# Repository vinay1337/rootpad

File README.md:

# rootpad
A 18 key macropad / numpad based on the atmega32u4 microcontroller

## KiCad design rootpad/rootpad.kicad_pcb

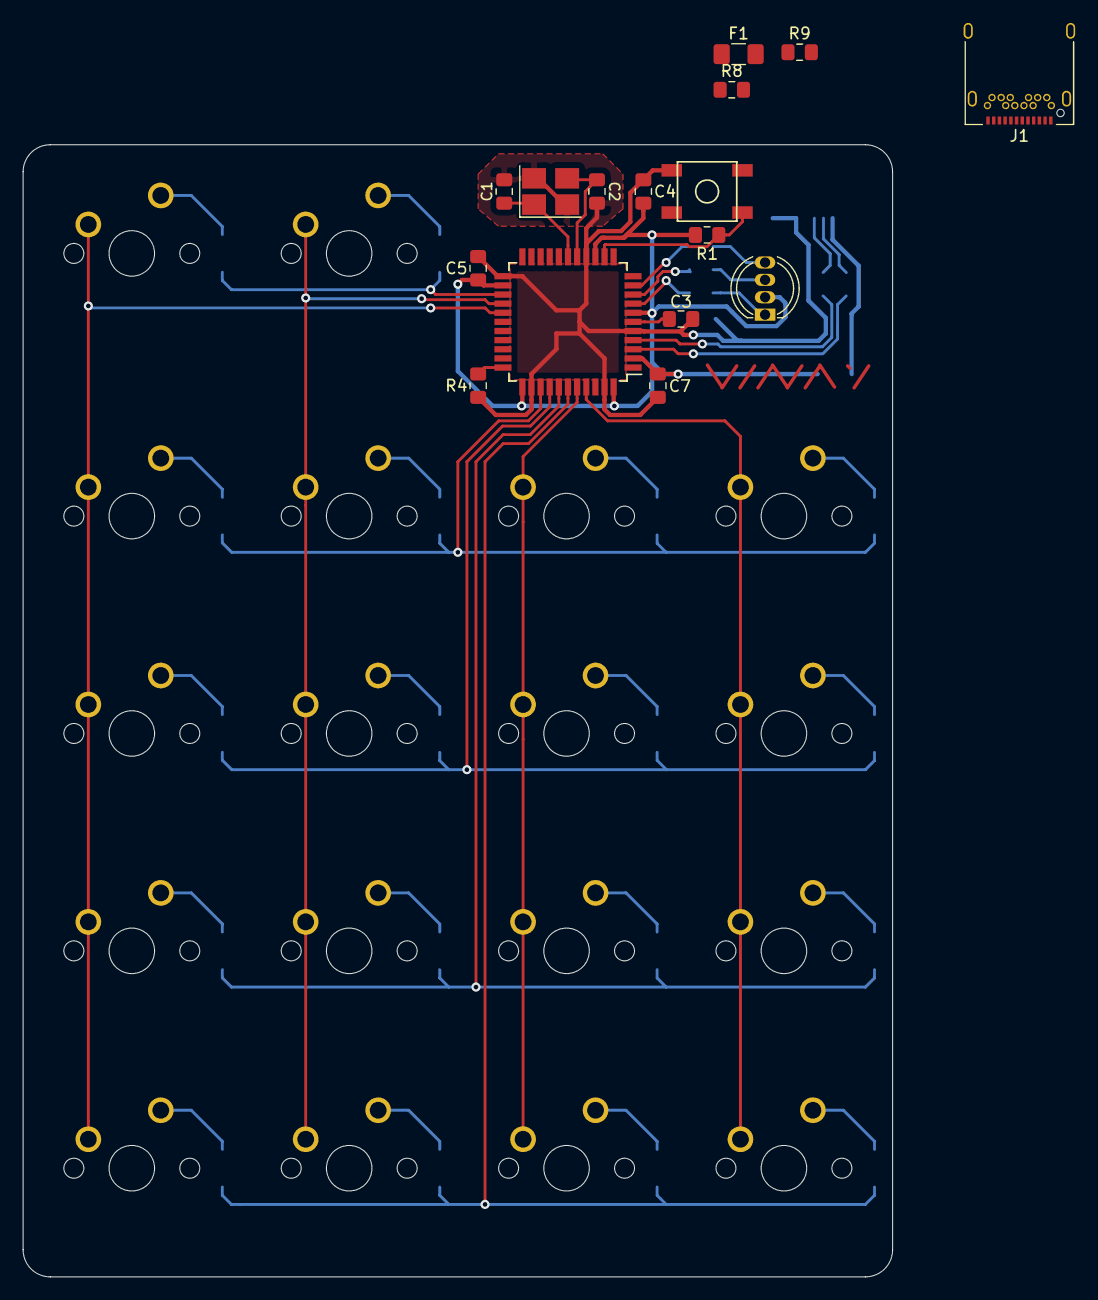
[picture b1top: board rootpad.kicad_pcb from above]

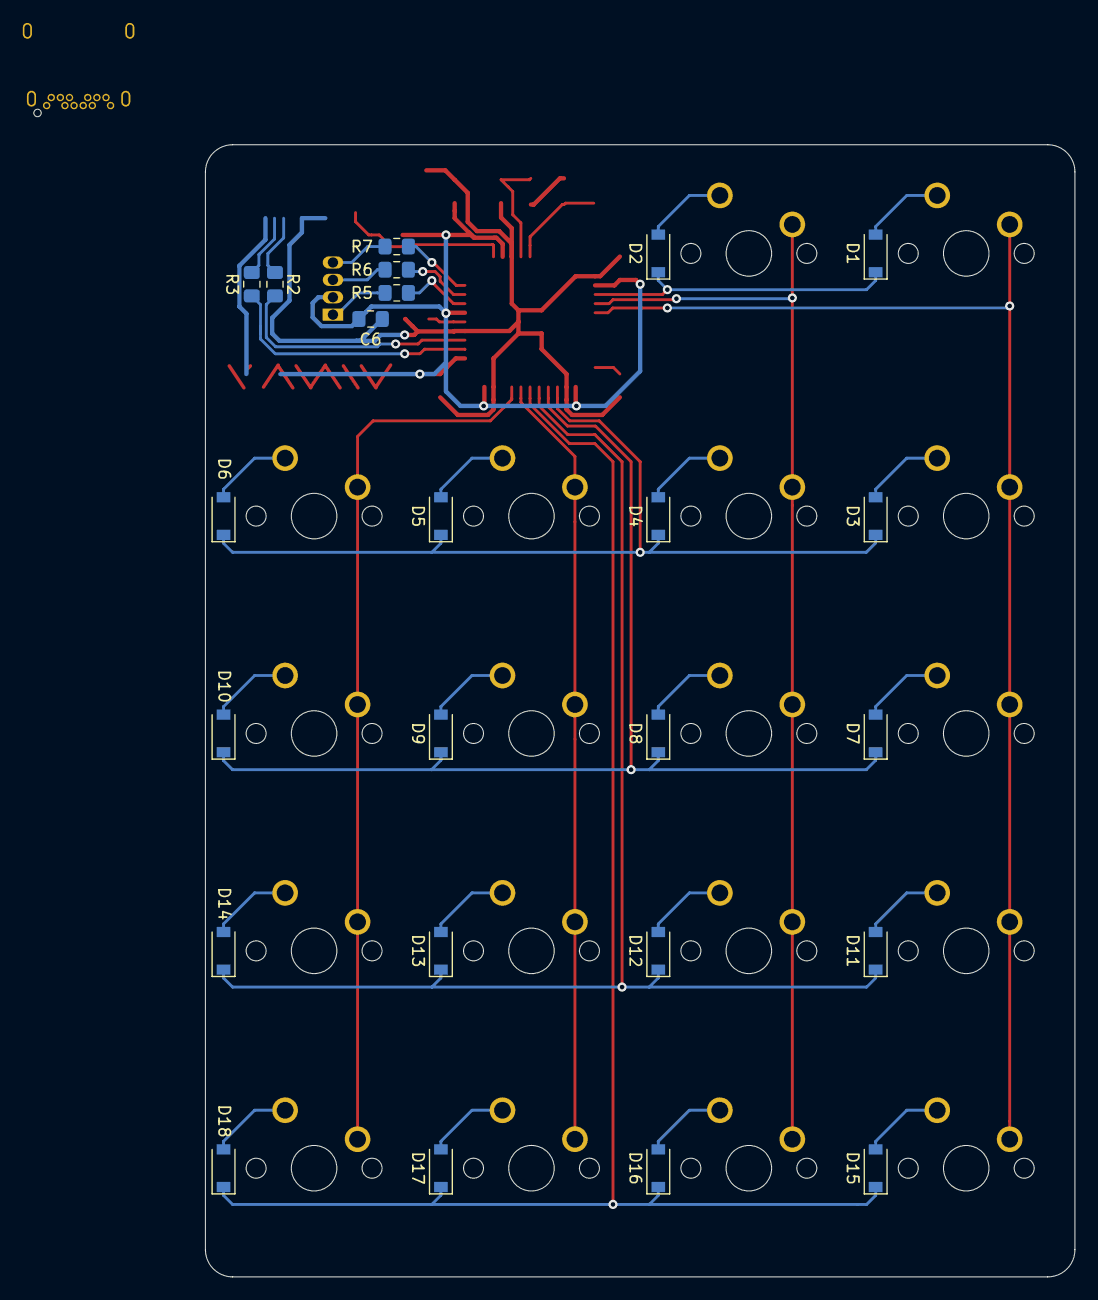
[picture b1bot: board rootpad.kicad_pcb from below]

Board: 2 copper layers, 76.2 x 99.2 mm, 58 parts (24 on the bottom side), 47 nets.

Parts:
C1, C2: 22pF; C_0805_2012Metric_Pad1.15x1.40mm_HandSolder
C3: 1uF; C_0805_2012Metric_Pad1.15x1.40mm_HandSolder
C4, C5, C6: 0.1uF; C_0805_2012Metric_Pad1.15x1.40mm_HandSolder
C7: 10uF; C_0805_2012Metric_Pad1.15x1.40mm_HandSolder
D1, D2, D3, D4, D5, D6, D7, D8, D9, D10, D11, D12, D13, D14, D15, D16, D17, D18: D_Small; D_SOD-123
D19: LED_RAGB; LED_D5.0mm-4_RGB_Spaced
F1: 500mA; Fuse_1206_3216Metric_Pad1.42x1.75mm_HandSolder
J1: USB_C_Receptacle_USB2.0; USB_C_Receptacle_Amphenol_12401548E4-2A
MX1, MX2, MX3, MX4, MX5, MX6, MX7, MX8, MX9, MX10, MX11, MX12, MX13, MX14, MX15, MX16, MX17, MX18: MX-NoLED; MXOnly-1U-NoLED
R1, R4: 10k; R_0805_2012Metric_Pad1.15x1.40mm_HandSolder
R2, R3: 22; R_0805_2012Metric_Pad1.15x1.40mm_HandSolder
R5: 150; R_0805_2012Metric_Pad1.15x1.40mm_HandSolder
R6, R7: 80; R_0805_2012Metric_Pad1.15x1.40mm_HandSolder
R8, R9: 5.1k; R_0805_2012Metric_Pad1.15x1.40mm_HandSolder
SW1: SW_Push; SKQG-1155865
U1: ATmega32U4-AU; TQFP-44_10x10mm_P0.8mm
Y1: 16MHz; Crystal_SMD_3225-4Pin_3.2x2.5mm_HandSoldering

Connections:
+5V: C4.1, C5.1, C6.1, C7.1, D19.2, F1.1, R1.1, U1.2, U1.7, U1.14, U1.24, U1.34, U1.44
COL0: MX1.1, MX3.1, MX7.1, MX11.1, MX15.1, U1.27
COL1: MX2.1, MX4.1, MX8.1, MX12.1, MX16.1, U1.26
COL2: MX5.1, MX9.1, MX13.1, MX17.1, U1.40
COL3: MX6.1, MX10.1, MX14.1, MX18.1, U1.41
D+: J1.A6, J1.B6, R2.2
D-: J1.A7, J1.B7, R3.1
GND: C1.2, C2.1, C3.2, C4.2, C5.2, C6.2, C7.2, J1.A1, J1.A12, J1.B1, J1.B12, J1.S1, R4.1, R8.1, R9.1, SW1.1, U1.5, U1.15, U1.23, U1.35, U1.43, Y1.2, Y1.4
LED_B: R7.2, U1.10
LED_G: R6.2, U1.9
LED_R: R5.2, U1.8
unnamed: C1.1, U1.17, Y1.1
unnamed: C2.2, U1.16, Y1.3
unnamed: C3.1, U1.6
unnamed: D1.2, MX1.2
unnamed: D2.2, MX2.2
unnamed: D3.2, MX3.2
unnamed: D4.2, MX4.2
unnamed: D5.2, MX5.2
unnamed: D6.2, MX6.2
unnamed: D7.2, MX7.2
unnamed: D8.2, MX8.2
unnamed: D9.2, MX9.2
unnamed: D10.2, MX10.2
unnamed: D11.2, MX11.2
unnamed: D12.2, MX12.2
unnamed: D13.2, MX13.2
unnamed: D14.2, MX14.2
unnamed: D15.2, MX15.2
unnamed: D16.2, MX16.2
unnamed: D17.2, MX17.2
unnamed: D18.2, MX18.2
unnamed: D19.1, R5.1
unnamed: D19.3, R6.1
unnamed: D19.4, R7.1
unnamed: J1.A5, R8.2
unnamed: J1.B5, R9.2
unnamed: R1.2, SW1.2, U1.13
unnamed: R2.1, U1.4
unnamed: R3.2, U1.3
unnamed: R4.2, U1.33
ROW0: D1.1, D2.1, U1.25
ROW1: D3.1, D4.1, D5.1, D6.1, U1.36
ROW2: D7.1, D8.1, D9.1, D10.1, U1.37
ROW3: D11.1, D12.1, D13.1, D14.1, U1.38
ROW4: D15.1, D16.1, D17.1, D18.1, U1.39
VCC: F1.2, J1.A4, J1.A9, J1.B4, J1.B9

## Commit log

2019-07-29 Initial Commit with dependencies
2019-07-29 Schematic and footprint assignments
2019-07-29 Laid out Matrix on PCB
2019-07-29 Placed MCU and caps around it
2019-08-07 Initial placement of all components
    Starting Routing
2019-08-07 Initial routing
2019-08-08 Finished route of mcu
2019-08-08 Initial route of matrix. Not connected
2019-08-08 Finished connection matrix to mcu
2019-08-08 Added and routed LED
2019-08-13 Completed routing and prettied up board
2019-08-13 Hid Y1 silkscreen
2019-08-14 Changed diode and reset footprints
2019-08-14 Connected diodes and reset
2019-08-14 Generated gerbers
2019-08-15 Updated Gerbers & increased width on LED
2019-08-20 Minor adjustments I think
2019-08-28 Moved libraries and implemented changes from ai03 branch
2019-08-28 Correctly routed reset button
    Diodes still need work done
2019-08-29 Routed Diodes, need to move name
2019-08-29 Cleared area for name and moved some silkscreen labels
2019-08-29 Mounting holes
2019-08-29 Rearranged switches to fit 100x100 mm pcb
2019-08-31 Routed MCU,XTAL,USB.RST
2019-08-31 Routed matrix and LED
2019-08-31 Arranged silkscreen, placed holes
2019-09-01 Minor routing tweaks
2019-09-01 Minor polishes
2019-09-01 Updated Gerbers
2019-09-01 Modified schematic, assigned footprints
